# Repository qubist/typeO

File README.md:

# typeO

e-paper typing software and hardware

## Background

For now, this repo is for collecting relevant information for the prototyping of the typeO using a remarkable and a keyboard.

## Pogo pin connector

The pogo pin connector is in prototype stage. The goal of this device is to provide keyboard access to the reMarkable 2 through the Pogo pins, which have OTG support (unlike the USB C port).

### Software

See [pogo-pin-software.md](/pogo-pin-software.md)

### Hardware

#### Prototype:

https://www.youtube.com/watch?v=7q5tBEi4npA

#### Parts list

- Pogo pin header:
   - Straight: https://www.digikey.com/en/products/detail/821-22-005-10-001101/ED8198-05-ND/1146577?itemSeq=360991255
   - Right-angle: https://www.digikey.com/en/products/detail/mill-max-manufacturing-corp/829-22-005-20-001101/2416226
   - Long: https://www.digikey.com/en/products/detail/mill-max-manufacturing-corp/816-22-005-10-003101/6149711
- USB C breakout: https://www.digikey.com/en/products/detail/4090/1528-2873-ND/9951930?itemSeq=360991872
- 5.1 kOhm resistor
- 1/8in x 1/2in magnets: https://www.kjmagnetics.com/proddetail.asp?prod=D28-N52&cat=168
- tiny dip switch on the PCB for hackability: https://www.digikey.com/en/products/detail/e-switch/KAE01SGGT/3749638

#### Circuit

[Prototype circuit diagram](pcb/prototype_circuit.fzz)

([Reference USB-C pinout](https://electronics.stackexchange.com/questions/291413/usb-c-to-usb-a-pinout/291427))

#### 3D printed part

The 3D printed part holds the magnets and pogo pin headers together and friction fits onto the remarkable. The magnets and flange help it align, and the pins should contact.

## Future

[Feature wishlist](/feature-wishlist.md)

## Other resources

[See also link collection](/sick-links.md)

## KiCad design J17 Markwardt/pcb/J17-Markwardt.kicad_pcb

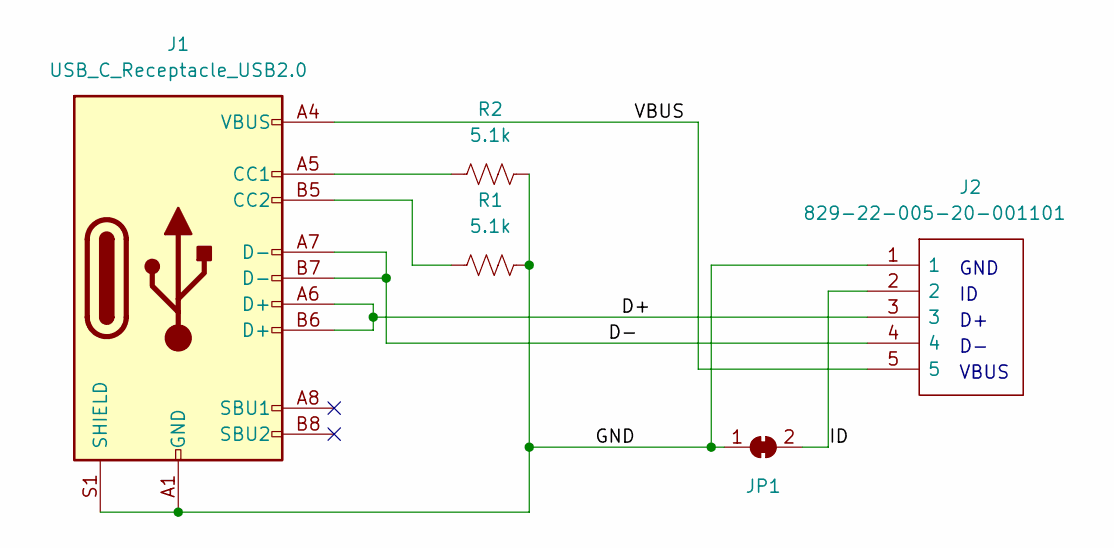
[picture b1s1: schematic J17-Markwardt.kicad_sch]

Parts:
J1: USB_C_Receptacle_USB2.0; USB_C_Receptacle_JAE_DX07S016JA1R1500
J2: 829-22-005-20-001101; 8292200520001101; Manufacturer_Part_Number 829-22-005-20-001101; Mouser Part Number 575-8292200520
JP1: (no value)
R1, R2: 5.1k; R_Axial_DIN0207_L6.3mm_D2.5mm_P7.62mm_Horizontal

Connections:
/D+: J1.A6 (D+), J1.B6 (D+), J2.3
/D-: J1.A7 (D-), J1.B7 (D-), J2.4
/GND: J1.A1 (GND), J1.A12 (GND), J1.B1 (GND), J1.B12 (GND), J1.S1 (SHIELD), J2.1, JP1.1 (A), R1.1, R2.1
/ID: J2.2, JP1.2 (B)
/VBUS: J1.A4 (VBUS), J1.A9 (VBUS), J1.B4 (VBUS), J1.B9 (VBUS), J2.5
unnamed: J1.A5 (CC1), R2.2
unnamed: J1.B5 (CC2), R1.2

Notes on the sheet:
VBUS
GND

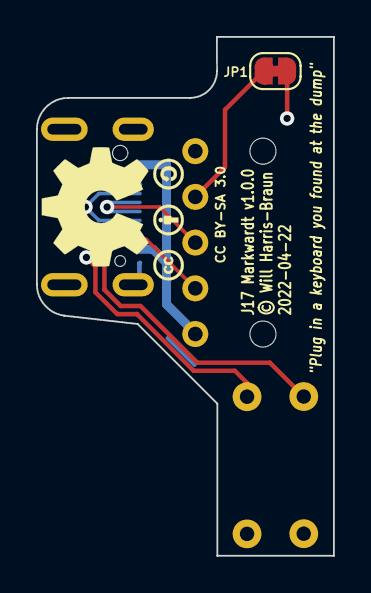
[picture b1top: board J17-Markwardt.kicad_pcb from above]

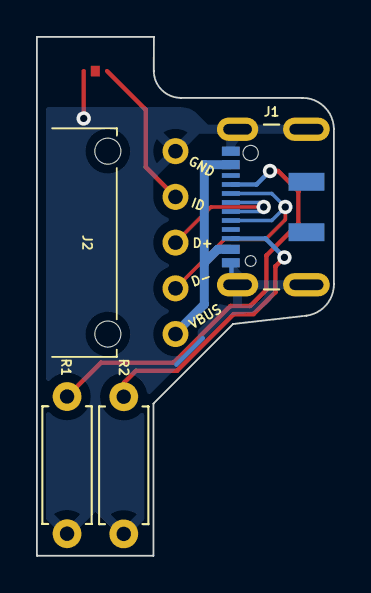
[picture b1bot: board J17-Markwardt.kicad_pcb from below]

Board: 2 copper layers, 16.5 x 28.8 mm, 5 parts (3 on the bottom side), 7 nets.

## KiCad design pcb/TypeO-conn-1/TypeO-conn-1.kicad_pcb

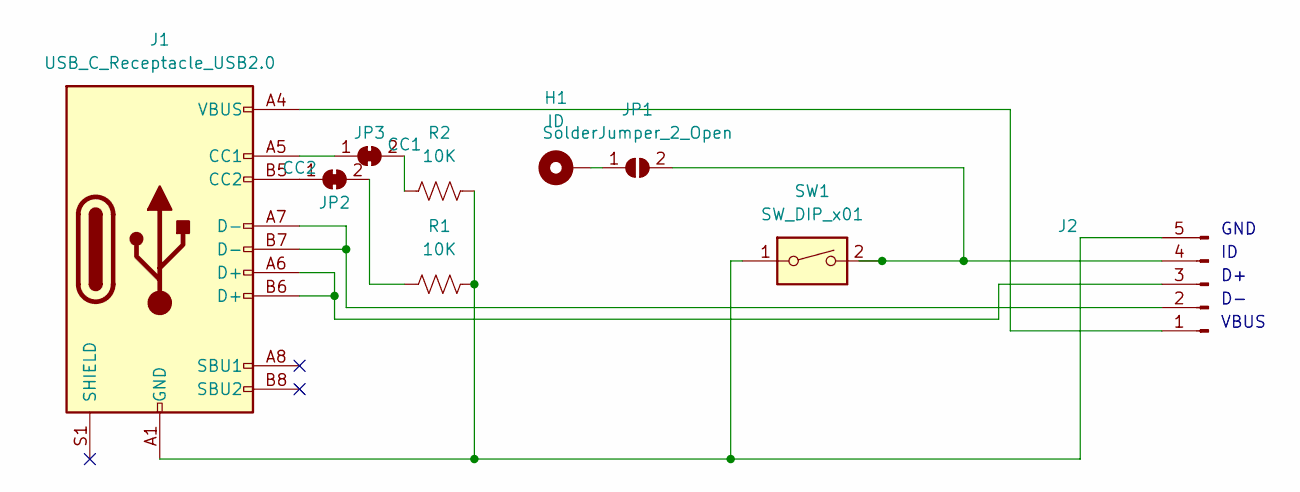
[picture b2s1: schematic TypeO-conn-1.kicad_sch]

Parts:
H1: ID; SolderWire-0.1sqmm_1x01_D0.4mm_OD1mm
J1: USB_C_Receptacle_USB2.0; USB_C_Receptacle_JAE_DX07S016JA1R1500
J2: (no value)
JP1: SolderJumper_2_Open; SolderJumper-2_P1.3mm_Open_TrianglePad1.0x1.5mm
JP2: CC2; SolderJumper-2_P1.3mm_Bridged_RoundedPad1.0x1.5mm
JP3: CC1; SolderJumper-2_P1.3mm_Bridged_RoundedPad1.0x1.5mm
R1, R2: 10K; R_Axial_DIN0207_L6.3mm_D2.5mm_P7.62mm_Horizontal
SW1: SW_DIP_x01; SW_DIP_SPSTx01_Slide_Omron_A6S-110x_W8.9mm_P2.54mm

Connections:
unnamed: H1.1, JP1.1 (A)
unnamed: J1.A1 (GND), J1.A12 (GND), J1.B1 (GND), J1.B12 (GND), J2.5, R1.1, R2.1, SW1.1
unnamed: J1.A4 (VBUS), J1.A9 (VBUS), J1.B4 (VBUS), J1.B9 (VBUS), J2.1
unnamed: J1.A5 (CC1), JP3.1 (A)
unnamed: J1.A6 (D+), J1.B6 (D+), J2.3
unnamed: J1.A7 (D-), J1.B7 (D-), J2.2
unnamed: J1.B5 (CC2), JP2.1 (A)
unnamed: J2.4, JP1.2 (B), SW1.2
unnamed: JP2.2 (B), R1.2
unnamed: JP3.2 (B), R2.2

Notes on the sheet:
VBUS
GND

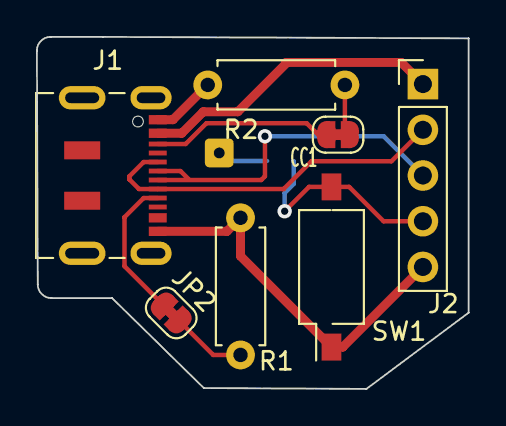
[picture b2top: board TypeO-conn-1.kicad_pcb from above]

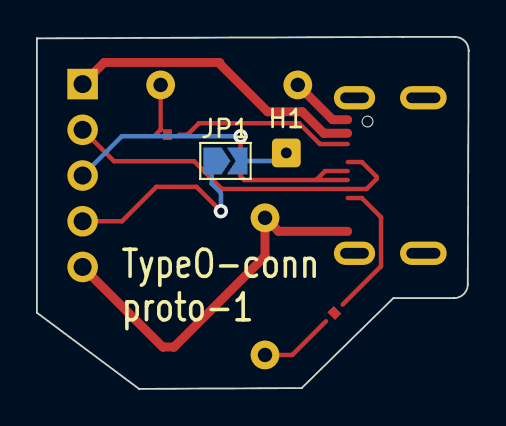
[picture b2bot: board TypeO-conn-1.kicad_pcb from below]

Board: 2 copper layers, 24.0 x 19.6 mm, 9 parts (2 on the bottom side), 10 nets.

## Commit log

2022-02-12 Change software file to markdown
2022-02-13 Add printed part info
2022-02-14 Compiled some sick links for reference, inspiration, connections, and instructions
2022-02-14 Add a feature wishlist document
2022-02-14 fixed asteriskss
2022-02-14 Add some wishlist items and link items
2022-02-14 Add waveshare link
2022-02-21 Add link
2022-03-04 Add MinuteEarth link
2022-03-08 Rename and add photos in gallery
2022-03-11 Add people file
    @MorvinBear check it
2022-03-13 Add auto-host-mode reference
2022-03-30 Add circuit
2022-03-30 Update PCB
2022-03-30 Update PCB to add jumpers
2022-04-01 Add a cronjob manual
2022-04-01 Formatting
2022-04-09 Split from wiki
2022-04-09 Change to single quotes
    This is actually important
2022-04-16 Reorganize
2022-04-18 "Sync TypeO-conn-1 changes"
2022-04-19 Change naming scheme for PCB design
    Will start using git tags to mark versions and just have one file. Git
    will save version history.
2022-04-19 Add new Pogo pin links
2022-04-19 Start work on typeO-conn v2
2022-04-19 Prettify circuit diagram and add to Readme
2022-04-19 Fix typo
2022-04-19 Change resistor values
2022-04-19 Update circuit diagram
2022-04-19 Start ignoring KiCad backups
2022-04-22 Rearrange and update silkscreen
2022-04-23 Add final edge cuts
2022-04-23 Add rounded, updated date
2022-04-23 Tweaks
2022-04-23 Rename connector to J17 Markwardt
2022-04-23 Update board a lil
2022-05-04 Add new Markwardt case with space for PCB

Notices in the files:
J17 Markwardt/pcb/J17-Markwardt.kicad_pcb:
© Will Harris-Braun
CC BY-SA 3.0
